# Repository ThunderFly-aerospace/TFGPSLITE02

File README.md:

# TFGPSLITE02 - Compact GNSS Module for Lightweight UAVs

The **TFGPSLITE02** module is a compact GNSS solution based on the [u-blox SAM-M8Q](https://www.u-blox.com/en/product/sam-m8q-module). It is designed for small, lightweight, and simple UAVs, offering excellent positioning accuracy with support for multiple satellite constellations. It connects seamlessly to flight controllers via the [Pixhawk standard "Basic GPS Port"](https://github.com/pixhawk/Pixhawk-Standards/blob/master/DS-009%20Pixhawk%20Connector%20Standard.pdf).

## Features

- **GNSS Support**: Concurrent reception of up to three GNSS systems (GPS, Galileo, GLONASS).
- **Compact Design**: Compact flat form factor with integrated patch antenna.
- **High Sensitivity**: Superior performance in environments with weak or obstructed GNSS signals.
- **Augmentation Systems**: Support for SBAS (WAAS, EGNOS, MSAS, GAGAN) and QZSS.
- **Advanced Security**:
  - Geofencing for operational boundaries.
  - Spoofing detection to enhance signal integrity.
  - Message integrity protection.
- **Wide Operational Range**:
  - Altitude: Up to 50,000 m.
  - Velocity: Up to 500 m/s.
  - Dynamic tolerance: Up to 4 g.
- **Built-in RTC**: Ensures faster Time-To-First-Fix (TTFF) after prolonged power-off periods.

## Technical Specifications

- **Interfaces**:
  - UART and I2C (via Basic GPS Port).
  - Time pulse output (1 PPS, configurable up to 10 MHz).
- **Power Supply**:
  - Main supply voltage: 5 V.
  - Typical current consumption is 30 mA.
- **GNSS Performance**:
  - Cold start TTFF: 26 s (GPS).
  - Hot start TTFF: 1 s.
  - Horizontal position accuracy: 2.5 m CEP.
- **Environmental Tolerances**:
  - Operating temperature: -40 °C to 85 °C.
  - Storage temperature: -40 °C to 85 °C.
- **Physical properties**: 
  - Dimensions 50x50x8mm
  - Weight 11.3 grams

## Connection to Flight Controller

The module interfaces with flight controllers using the Pixhawk standard **Basic GPS Port**. The port pinout is as follows:

| Pin | Signal    | Voltage |
|-----|-----------|---------|
| 1   | VCC       | +5V     |
| 2   | TX (OUT)  | +3.3V   |
| 3   | RX (IN)   | +3.3V   |
| 4   | I2C SCL   | +3.3V   |
| 5   | I2C SDA   | +3.3V   |
| 6   | GND       | GND     |

## Connection to payload

The module interfaces with the payload with the following signals:

| Pin | Signal    | Voltage |
|-----|-----------|---------|
| 1   | VCC       | +5V     |
| 2   | EXTINT (IN)  | +3.3V   |
| 3   | TPL (OUT)   | +3.3V   |
| 4   | GND       | GND     |

## Where to get it?

The TFGPSLITE02 is commercially available from [ThunderFly s.r.o.](https://www.thunderfly.cz/). For a commercial quotation, contact us by email at sale@thunderfly.cz or shop at our [Tindie store](https://www.tindie.com/stores/thunderfly/).

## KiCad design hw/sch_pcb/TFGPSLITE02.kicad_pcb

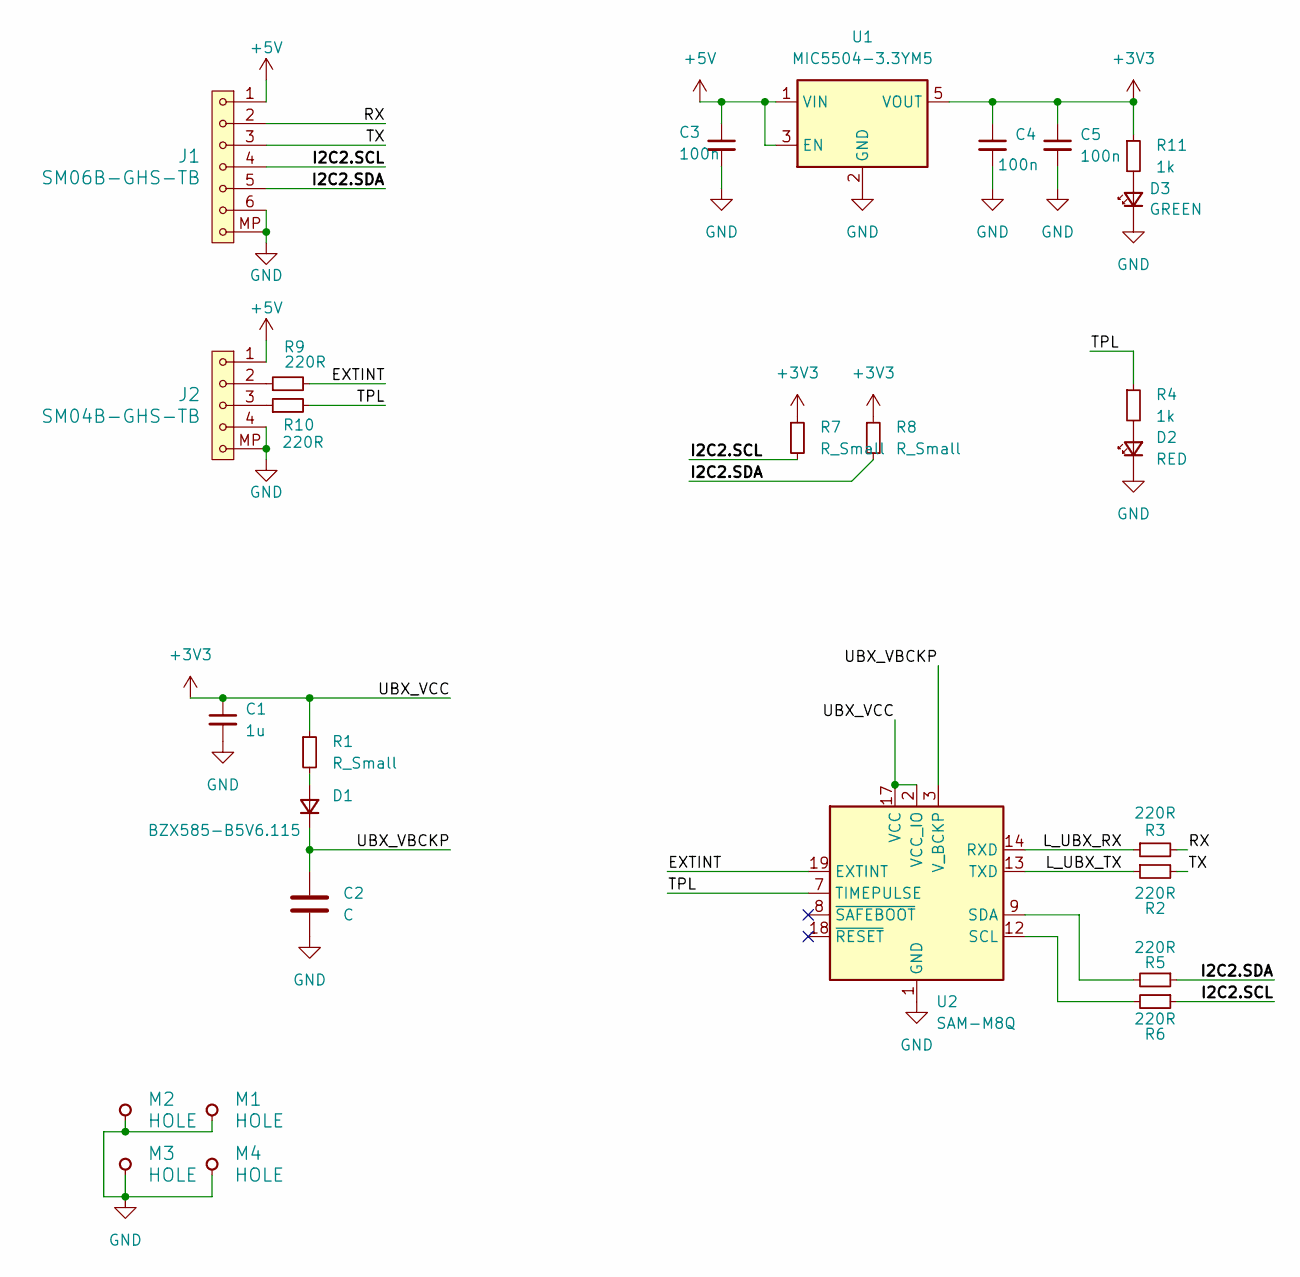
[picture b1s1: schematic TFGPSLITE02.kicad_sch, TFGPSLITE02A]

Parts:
C1: 1u; C_0805_2012Metric
C2: C; R_1206_3216Metric
C3, C4, C5: 100n; C_0805_2012Metric
D1: BZX585-B5V6.115; D_SOD-523
D2: RED; LED_0603_1608Metric
D3: GREEN; LED_0603_1608Metric
J1: SM06B-GHS-TB; JST_GH_SM06B-GHS-TB_1x06-1MP_P1.25mm_Horizontal
J2: SM04B-GHS-TB; JST_GH_SM04B-GHS-TB_1x04-1MP_P1.25mm_Horizontal
M1, M2, M3, M4: HOLE; MountingHole_3.2mm_M3_DIN965_Pad
R1, R7, R8: R_Small; R_0805_2012Metric
R2, R3, R5, R6, R9, R10: 220R; R_0805_2012Metric
R4, R11: 1k; R_0805_2012Metric
U1: MIC5504-3.3YM5; SOT-23-5
U2: SAM-M8Q; ublox_SAM-M8Q

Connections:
+3V3: C1.1, C4.1, C5.1, R1.1, R7.1, R8.1, R11.1, U1.5 (VOUT), U2.2 (VCC_IO), U2.17 (VCC)
+5V: C3.1, J1.1, J2.1, U1.1 (VIN), U1.3 (EN)
/EXTINT: R9.2, U2.19 (EXTINT)
/I2C2.SCL: J1.4, R6.1, R7.2
/I2C2.SDA: J1.5, R5.1, R8.2
/L_UBX_RX: R3.1, U2.14 (RXD)
/L_UBX_TX: R2.1, U2.13 (TXD)
/RX: J1.2, R3.2
/TPL: R4.1, R10.2, U2.7 (TIMEPULSE)
/TX: J1.3, R2.2
/UBX_VBCKP: C2.1, D1.1 (K), U2.3 (V_BCKP)
GND: C1.2, C2.2, C3.2, C4.2, C5.2, D2.1 (K), D3.1 (K), J1.6, J1.MP, J2.4, J2.MP, M1.1, M2.1, M3.1, M4.1, U1.2 (GND), U2.1 (GND), U2.4 (GND), U2.5 (GND), U2.6 (GND), U2.10 (GND), U2.11 (GND), U2.15 (GND), U2.16 (GND), U2.20 (GND)
unnamed: D1.2 (A), R1.2
unnamed: D2.2 (A), R4.2
unnamed: D3.2 (A), R11.2
unnamed: J2.2, R9.1
unnamed: J2.3, R10.1
unnamed: R6.2, U2.12 (SCL)
unnamed: R5.2, U2.9 (SDA)

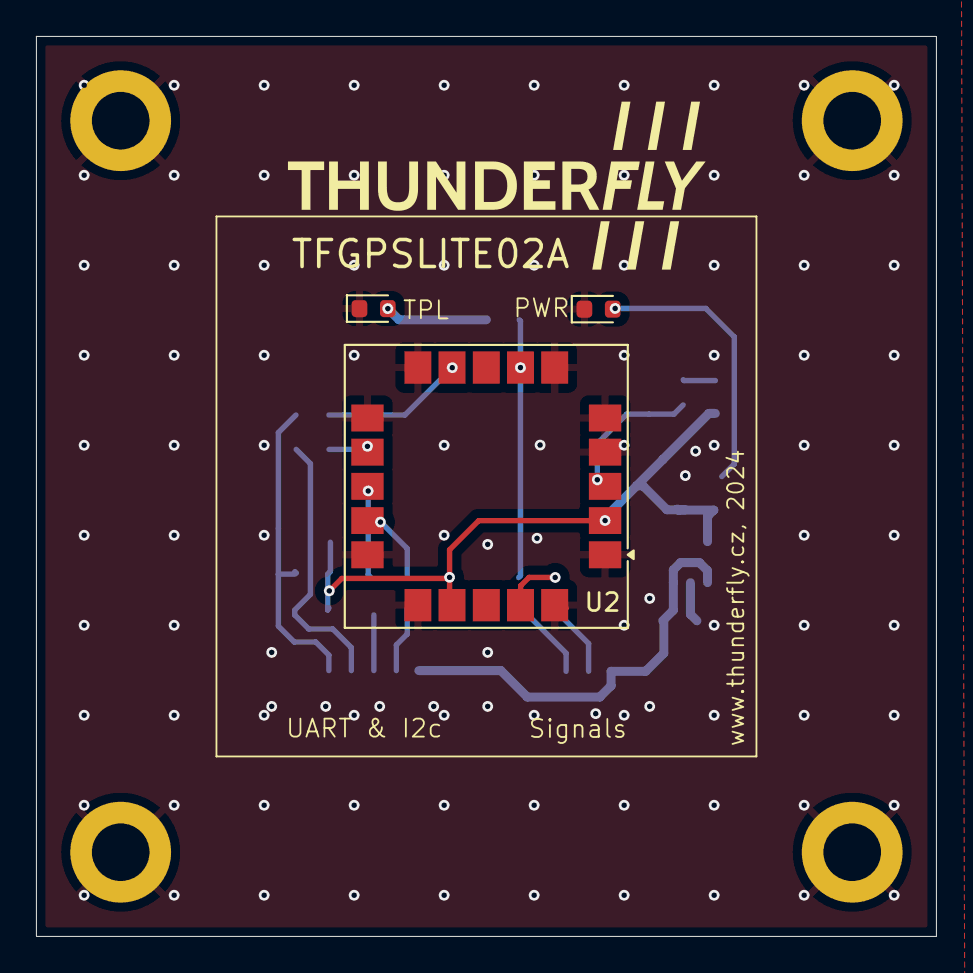
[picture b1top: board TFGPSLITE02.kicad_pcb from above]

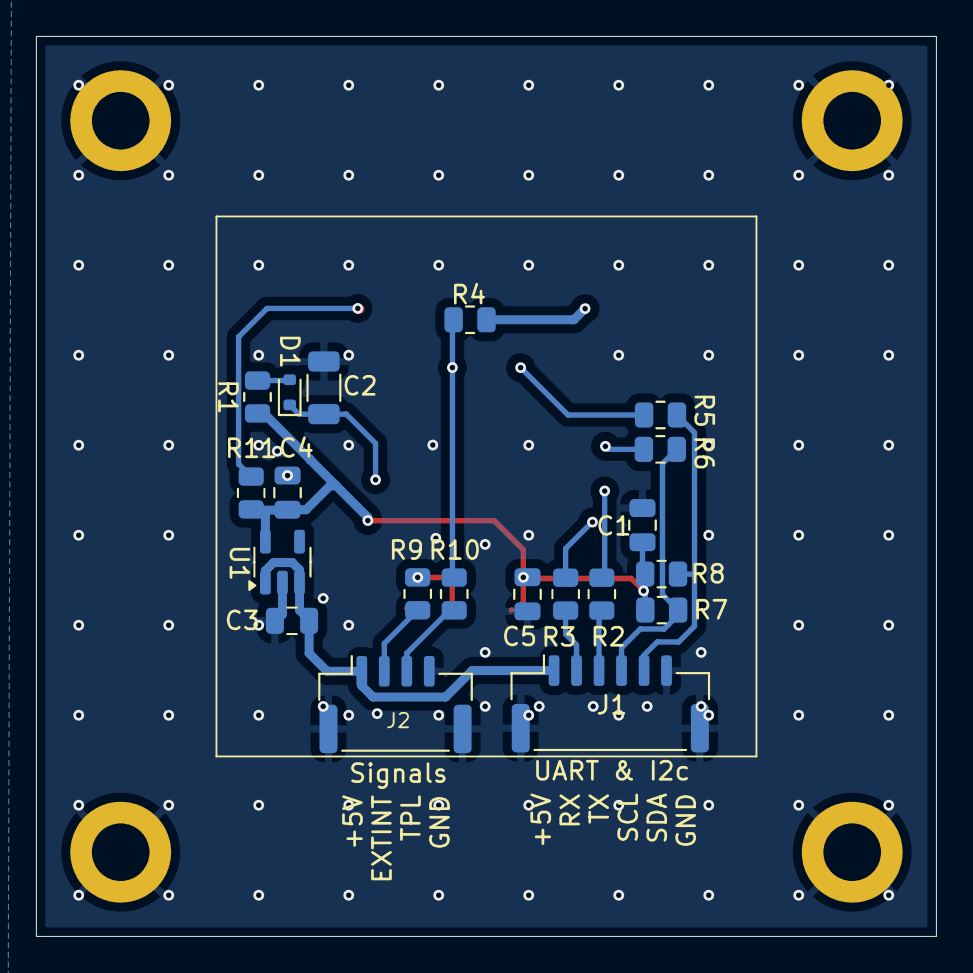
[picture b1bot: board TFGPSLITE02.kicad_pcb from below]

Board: 2 copper layers, 50.0 x 50.0 mm, 27 parts (20 on the bottom side), 19 nets.

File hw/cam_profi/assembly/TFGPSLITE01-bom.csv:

Component,Description,Part,References,Value,Footprint,Quantity Per PCB,Datasheet,ust_id,sim.device,sim.pins,manufacturer_name,manufacturer_part_number
1,"Unpolarized capacitor, small symbol",C_Small,C3C4,100n,C_0805_2012Metric,2,~,5c70984812875079b91f8bf2,,,,
2,"Unpolarized capacitor, small symbol",C_Small,C1,1u,C_0805_2012Metric,1,~,5c70984812875079b91f8bc3,,,,
3,Unpolarized capacitor,C,C2,C,R_1206_3216Metric,1,~,,,,,
4,"Diode, small symbol",D_Small,D1,BZX585-B5V6.115,D_SOD-523,1,~,,D,1=K 2=A,,
5,"Light emitting diode, small symbol",LED_Small,D3,GREEN,LED_0603_1608Metric,1,~,60d582331287500165f859d0,,,,
6,"Light emitting diode, small symbol",LED_Small,D2,RED,LED_0603_1608Metric,1,~,60d582331287500165f859d0,,,,
7,Concurrent GNSS Antenna Modules,CAM-M8Q,IC1,CAM-M8Q,CAM-M8Q,1,https://www.u-blox.com/sites/default/files/CAM-M8-FW3_DataSh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,669a6e3c6fdfe6f54e2eb4be,,,U-Blox,CAM-M8Q
8,,SM04B-GHS-TB,J2,SM04B-GHS-TB,JST_GH_SM04B-GHS-TB_1x04-1MP_P1.25mm_Horizontal,1,,,,,,
9,1x07 2.54 mm pitch header,SM06B-GHS-TB,J1,SM06B-GHS-TB,JST_GH_SM06B-GHS-TB_1x06-1MP_P1.25mm_Horizontal,1,,,,,,
10,"Resistor, small symbol",R_Small,R2R3R5R6R9R10,220R,R_0805_2012Metric,6,~,5c70984512875079b91f8958,,,,
11,"Resistor, small symbol",R_Small,R4R11,1k,R_0805_2012Metric,2,~,5c70984512875079b91f895c,,,,
12,"Resistor, small symbol",R_Small,R1R7R8,R_Small,R_0805_2012Metric,3,~,,,,,
13,"300mA Low-dropout Voltage Regulator, Vout 3.3V, Vin up to 5.5V, SOT-23",MIC5504-3.3YM5,U1,MIC5504-3.3YM5,SOT-23-5,1,http://ww1.microchip.com/downloads/en/DeviceDoc/MIC550X.pdf,5c7255e81287500b4e112ea2,,,,

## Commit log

2024-10-13 update assets, initial commit of kicad files
2024-10-13 update assets
2024-10-14 solve DRC, silkscreen
2024-10-18 update actions
2024-10-18 repair assets folder
2024-10-18 Update workflow files
2024-10-18 Update actions products
2024-11-07 Design of TFGPSLITE01
2024-11-07 improve layout
2025-01-01 Improve documentation.
2025-01-11 Update schematics and PCB title blocks.
2025-01-11 Update documentation.
2025-01-11 Add tindie listing.
2025-02-06 Improve description.
